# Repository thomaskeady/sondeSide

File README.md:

# sondeSide
Sonde electronics for JHU ASCO lab

Created using EAGLE 9.1.2 
https://www.autodesk.com/products/eagle/overview

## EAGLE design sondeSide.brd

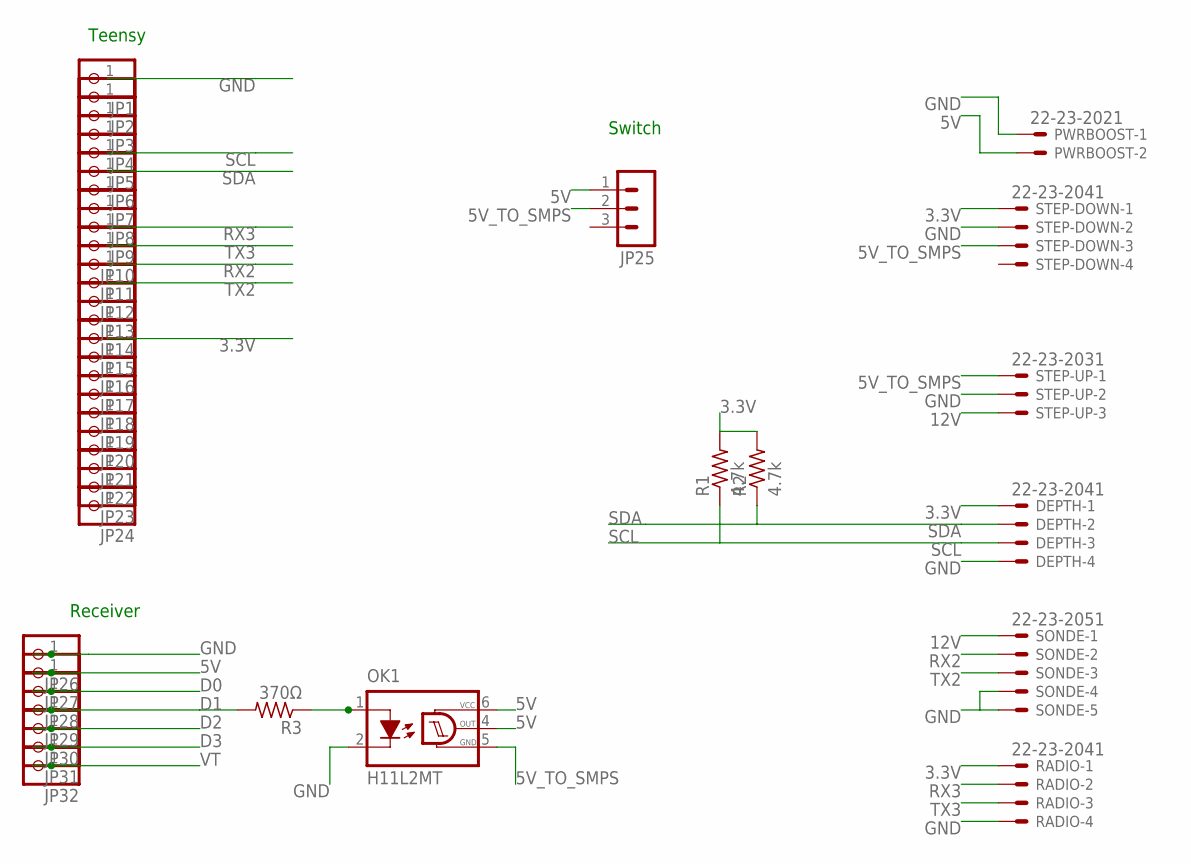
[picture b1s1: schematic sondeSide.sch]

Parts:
DEPTH: 22-23-2041
JP1, JP2, JP3, JP4, JP5, JP6, JP7, JP8, JP9, JP10, JP11, JP12, JP13, JP14, JP15, JP16, JP17, JP18, JP19, JP20, JP21, JP22, JP23, JP24, JP26, JP27, JP28, JP29, JP30, JP31, JP32: PINHD-1X1; 1X01
JP25: MA03-1
OK1: H11L2MT; DIL6-04
PWRBOOST: 22-23-2021
R1, R2: 4.7k; 0204/7
R3: 370Ω; 0204V
RADIO: 22-23-2041
SONDE: 22-23-2051
STEP-DOWN: 22-23-2041
STEP-UP: 22-23-2031

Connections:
3.3V: DEPTH.1, JP15.1, R1.2, R2.2, RADIO.1, STEP-DOWN.1
5V: JP25.1, JP27.1, OK1.4 (OUT), OK1.6 (VCC), PWRBOOST.2
5V_TO_SMPS: JP25.2, OK1.5 (GND), STEP-DOWN.3, STEP-UP.1
12V: SONDE.1, STEP-UP.3
D0: JP28.1
D1: JP29.1, R3.2
D2: JP30.1
D3: JP31.1
GND: DEPTH.4, JP1.1, JP26.1, OK1.2 (C), PWRBOOST.1, RADIO.4, SONDE.4, SONDE.5, STEP-DOWN.2, STEP-UP.2
unnamed: OK1.1 (A), R3.1
RX2: JP11.1, SONDE.2
RX3: JP9.1, RADIO.2
SCL: DEPTH.3, JP5.1, R1.1
SDA: DEPTH.2, JP6.1, R2.1
TX2: JP12.1, SONDE.3
TX3: JP10.1, RADIO.3
VT: JP32.1

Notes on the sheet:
Teensy
Receiver
Switch

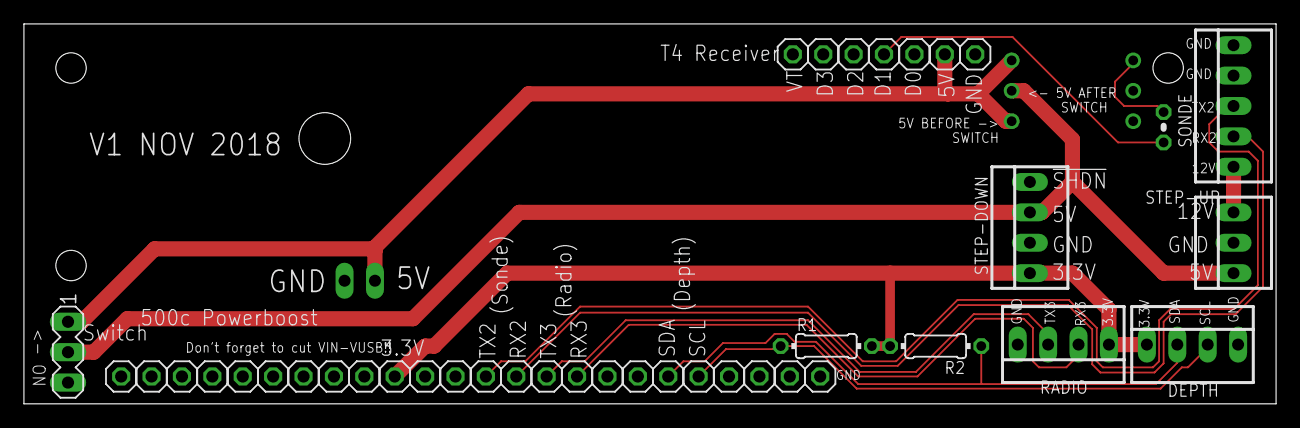
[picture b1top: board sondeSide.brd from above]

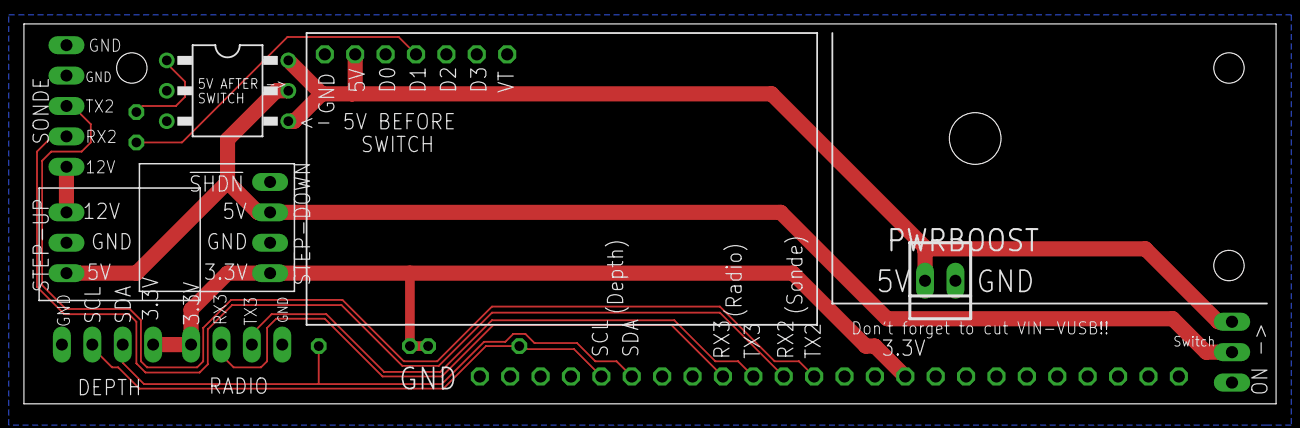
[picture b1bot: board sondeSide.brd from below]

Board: 2 copper layers, 104.6 x 31.8 mm, 42 parts (2 on the bottom side), 13 nets.

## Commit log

2018-10-15 I think its done, just needs labels
2018-10-15 I think its done
2018-10-15 Without external 3.3v step down
2018-10-15 Pre-routing
2018-10-15 Everything but ground plane
2018-10-15 Looking good just need to add 500c holes
2018-10-15 Finally ready to send with holes and everything
2018-10-15 Added powerboost silkscreen label
2018-10-22 Before adding the remote board
2018-10-31 Proposed layout, routing time
2018-10-31 About to do significant rerouting
2018-10-31 If we can swap the serial ports, good to go
2018-10-31 Good to go! Just place labels
2018-10-31 Flipped sonde connector
2018-10-31 Board is good to go
2018-11-04 Last push before switching to live-switch SSR
2018-11-05 Electrically ready to go
2018-11-05 Done with labels! Just would like to increase clearance on the ground pane
2018-11-05 Before flipping T4
2018-11-05 Moved all components to bottom
2018-11-06 I think ready to order!
2018-11-06 Final board for printing
2018-11-06 Moved one silkscreen
